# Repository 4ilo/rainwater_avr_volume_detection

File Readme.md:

# Rainwater volume monitor

Volume monitor module for 2 rainwater tanks.

Specifications:
- Atmega328p MCU
- Siemens SITRANS LH300 Hydrostatic Sensor
- HD44780 Lcd display

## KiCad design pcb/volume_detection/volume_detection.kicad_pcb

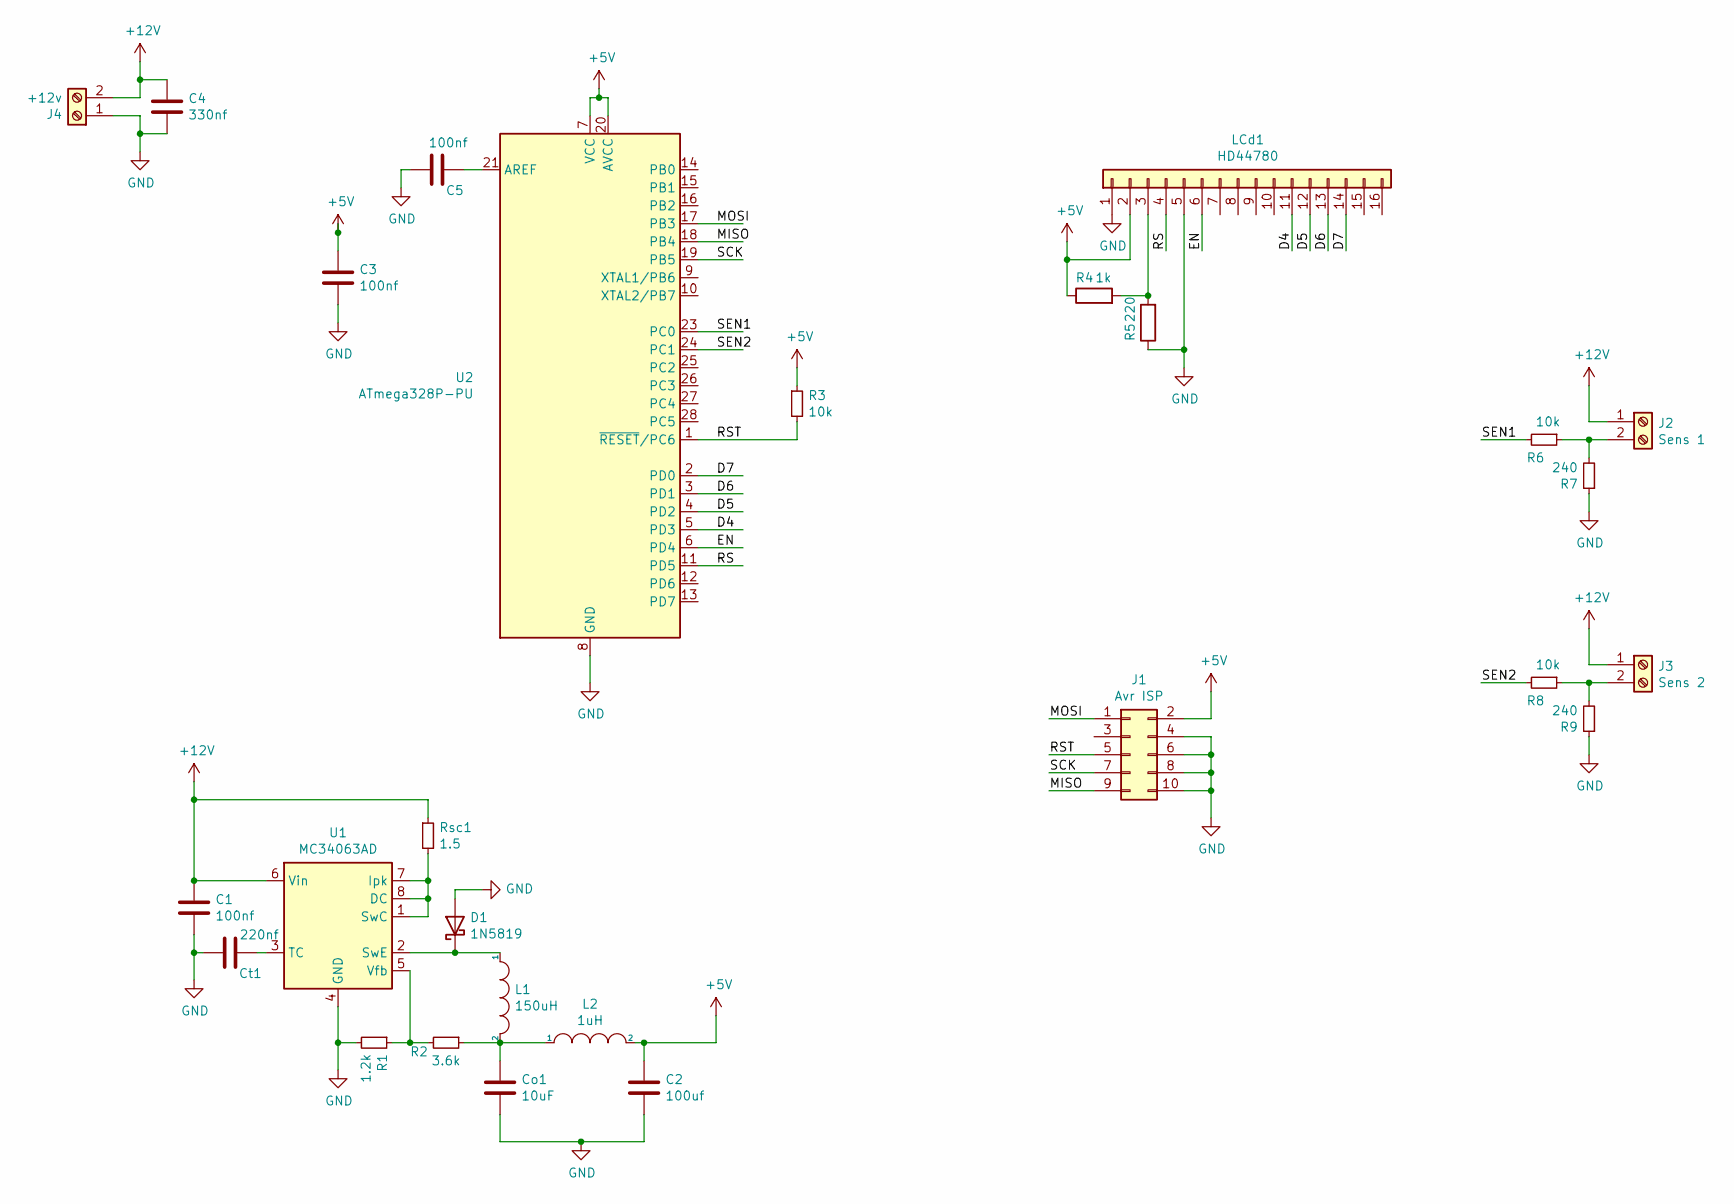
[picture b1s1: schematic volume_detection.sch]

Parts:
C1, C3, C5: 100nf; C_0805_2012Metric_Pad1.15x1.40mm_HandSolder
C2: 100uf; C_0805_2012Metric_Pad1.15x1.40mm_HandSolder
C4: 330nf; C_0805_2012Metric_Pad1.15x1.40mm_HandSolder
Co1: 10uF; CP_Elec_4x5.4
Ct1: 220nf; C_0805_2012Metric_Pad1.15x1.40mm_HandSolder
D1: 1N5819; D_DO-41_SOD81_P10.16mm_Horizontal
J1: Avr ISP; PinHeader_2x05_P2.54mm_Horizontal
J2: Sens 1; TerminalBlock_MetzConnect_Type055_RT01502HDWU_1x02_P5.00mm_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
J3: Sens 2; TerminalBlock_MetzConnect_Type055_RT01502HDWU_1x02_P5.00mm_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
J4: +12v; TerminalBlock_MetzConnect_Type055_RT01502HDWU_1x02_P5.00mm_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
L1: 150uH; L_Axial_L7.0mm_D3.3mm_P5.08mm_Vertical_Fastron_MICC
L2: 1uH; L_Axial_L6.6mm_D2.7mm_P10.16mm_Horizontal_Vishay_IM-2
LCd1: HD44780; PinHeader_1x16_P2.54mm_Vertical
R1: 1.2k; R_0805_2012Metric_Pad1.15x1.40mm_HandSolder
R2: 3.6k; R_0805_2012Metric_Pad1.15x1.40mm_HandSolder
R3, R6, R8: 10k; R_0805_2012Metric_Pad1.15x1.40mm_HandSolder
R4: 1k; R_0805_2012Metric_Pad1.15x1.40mm_HandSolder
R5: 220; R_0805_2012Metric_Pad1.15x1.40mm_HandSolder
R7, R9: 240; R_0805_2012Metric_Pad1.15x1.40mm_HandSolder
Rsc1: 1.5; R_0805_2012Metric_Pad1.15x1.40mm_HandSolder
U1: MC34063AD; SOIC-8_3.9x4.9mm_P1.27mm
U2: ATmega328P-PU; DIP-28_W7.62mm

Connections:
+5V: C2.1, C3.1, J1.2, L2.2, LCd1.2, R3.1, R4.1, U2.7 (VCC), U2.20 (AVCC)
+12V: C1.1, C4.1, J2.1, J3.1, J4.2, Rsc1.1, U1.6 (Vin)
/D4: LCd1.11, U2.5 (PD3)
/D5: LCd1.12, U2.4 (PD2)
/D6: LCd1.13, U2.3 (PD1)
/D7: LCd1.14, U2.2 (PD0)
/EN: LCd1.6, U2.6 (PD4)
/MISO: J1.9, U2.18 (PB4)
/MOSI: J1.1, U2.17 (PB3)
/RS: LCd1.4, U2.11 (PD5)
/RST: J1.5, R3.2, U2.1 (~RESET~/PC6)
/SCK: J1.7, U2.19 (PB5)
/SEN1: R6.2, U2.23 (PC0)
/SEN2: R8.2, U2.24 (PC1)
GND: C1.2, C2.2, C3.2, C4.2, C5.2, Co1.2, Ct1.2, D1.2 (A), J1.4, J1.6, J1.8, J1.10, J4.1, LCd1.1, LCd1.5, R1.2, R5.1, R7.1, R9.1, U1.4 (GND), U2.8 (GND), U2.22 (GND)
unnamed: C5.1, U2.21 (AREF)
unnamed: Co1.1, L1.2, L2.1, R2.1
unnamed: Ct1.1, U1.3 (TC)
unnamed: D1.1 (K), L1.1, U1.2 (SwE)
unnamed: J2.2, R6.1, R7.2
unnamed: J3.2, R8.1, R9.2
unnamed: LCd1.3, R4.2, R5.2
unnamed: R1.1, R2.2, U1.5 (Vfb)
unnamed: Rsc1.2, U1.1 (SwC), U1.7 (Ipk), U1.8 (DC)

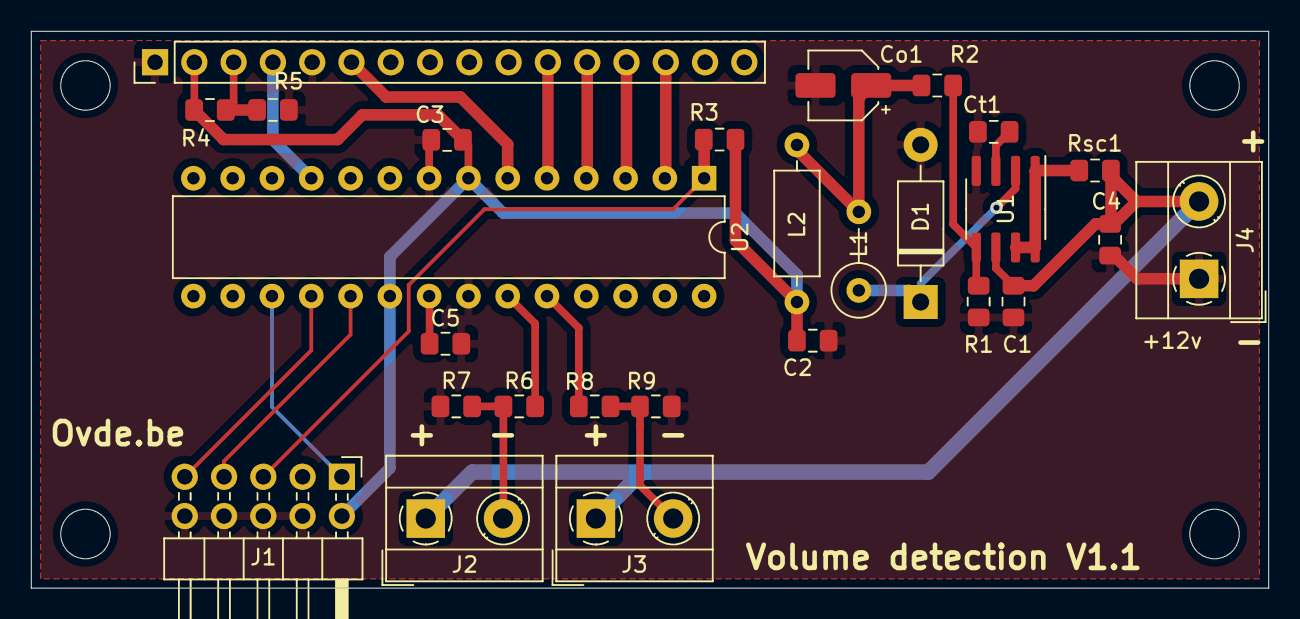
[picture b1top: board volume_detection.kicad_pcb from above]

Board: 2 copper layers, 80.0 x 36.0 mm, 27 parts (0 on the bottom side), 24 nets.

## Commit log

2020-08-09 Add avr gpio driver
2020-08-09 add readme
2020-08-11 Add lcd driver
2020-08-15 Add mcu and regulator to schematic
2020-08-16 finish schematic
2020-08-16 Finish pcb
2020-09-04 add pcb pdf
2020-09-05 update pcb
2020-09-06 update pcb + adc driver
2021-01-17 Update pcb + some code
